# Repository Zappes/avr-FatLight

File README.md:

The FatLight
======================================

What Is this?
-------------
Short: It's a controller board for RGB LED strips that has a bluetooth and some GPIO pins.

Long: I recently ordered everything needed for the creation of PCBs, i.e. a UV exposure unit,
an etching apparatus, chemicals, boards, the works. As a first project, I wanted to do something
that I could use, that I understood from the electronics perspective and that could easily be
done on a one-sided PCB without solder mask. A controller for RGB strips seemed to be a good idea, so here we go. :)

**WARNING IF YOU WANT TO BUILD THIS**
Make sure that the pinout of your Bluetooth module matches the pinout on the board. I have three different HC-05 modules in my parts bin, and every type has a different pinout ... This sucks enormously, and if I didn't have those modules lying around, I'd use a pure HC-05 module instead of the breakouts i have now.

How can I control it?
---------------------
It's simple. Connect to the FatLight using a serial terminal over the Bluetooth connection, connection parameters are 9600 8N1, no handshake. The modules have their default pin set to 1234, so use that pin. After connecting, the following commands are supported:

| Command    | Parameter | Description                           |
|------------|-----------|---------------------------------------|
| status     |           | Prints the current settings.          |
| mode       | 0-2       | 0: direct color, 1: fade, 2: random   |
| on         |           | Switches the light on                 | 
| off        |           | Switches the light off                |
| step       | 00-FF     | Size of the fading steps when fading  |
| set        | color     | Sets the target color in mode 0 and 1 |
| delay      | 00-FF     | Greater delays make slower fades      |
| level      | 00-FF     | Brightness in mode 2; 0 is random     |
| store      | 00-05     | Store current settings in slot 0-5    |
| load       | 00-05     | Load settings from slot 0-5           |   
| bt_getname |           | Prints the name of the BT module      |
| bt_setname | string    | Sets the name of the BT module        |
| bt_getpass |           | Prints the current BT PIN             |
| bt_setpass | string    | Sets the BT PIN; best use 4 digits    |

Color parameters are given as 24 bit hex codes, i.e. 00FF00 for green. Other numeric parameters are also in hex notation. String parameters may never contain whitespace.

Where can I learn more?
-----------------------
[There's a playlist on Youtube.](https://www.youtube.com/playlist?list=PLFFlJlvZ--Pn7IzDO5DFNhvppb0ZImLEq) It's in German, I'm afraid.

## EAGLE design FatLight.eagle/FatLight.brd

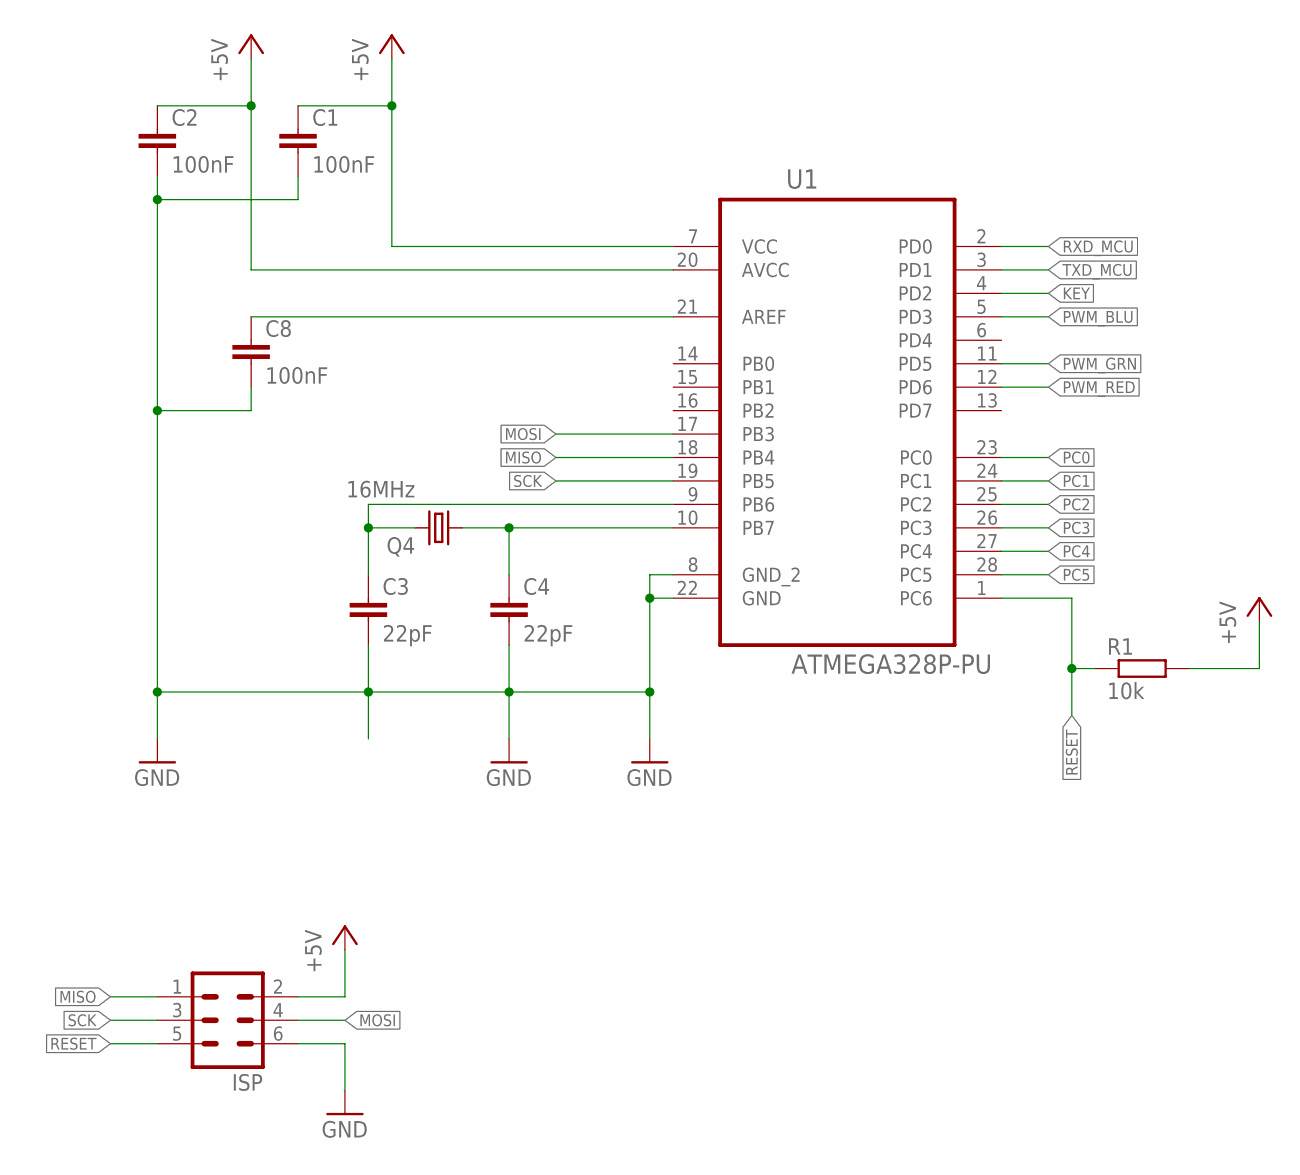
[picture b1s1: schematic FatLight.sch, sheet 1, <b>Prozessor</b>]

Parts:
C1, C2, C8: 100nF; C025-025X050
C3, C4: 22pF; C025-025X050
ISP: ML6
Q4: 16MHz; HC49/S
R1: 10k; 0207/7
U1: ATMEGA328P-PU; DIP254P762X457-28

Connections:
+5V: C1.1, C2.1, ISP.2, R1.2, U1.7 (VCC), U1.20 (AVCC); also elsewhere on the board
GND: C1.2, C2.2, C3.2, C4.2, C8.2, ISP.6, U1.8 (GND_2), U1.22 (GND); also elsewhere on the board
KEY: U1.4 (PD2); also elsewhere on the board
MISO: ISP.1, U1.18 (PB4)
MOSI: ISP.4, U1.17 (PB3)
unnamed: C4.1, Q4.1, U1.10 (PB7)
unnamed: C3.1, Q4.2, U1.9 (PB6)
unnamed: C8.1, U1.21 (AREF)
PC0: U1.23 (PC0); also elsewhere on the board
PC1: U1.24 (PC1); also elsewhere on the board
PC2: U1.25 (PC2); also elsewhere on the board
PC3: U1.26 (PC3); also elsewhere on the board
PC4: U1.27 (PC4); also elsewhere on the board
PC5: U1.28 (PC5); also elsewhere on the board
PWM_BLU: U1.5 (PD3); also elsewhere on the board
PWM_GRN: U1.11 (PD5); also elsewhere on the board
PWM_RED: U1.12 (PD6); also elsewhere on the board
RESET: ISP.5, R1.1, U1.1 (PC6)
RXD_MCU: U1.2 (PD0); also elsewhere on the board
SCK: ISP.3, U1.19 (PB5)
TXD_MCU: U1.3 (PD1); also elsewhere on the board

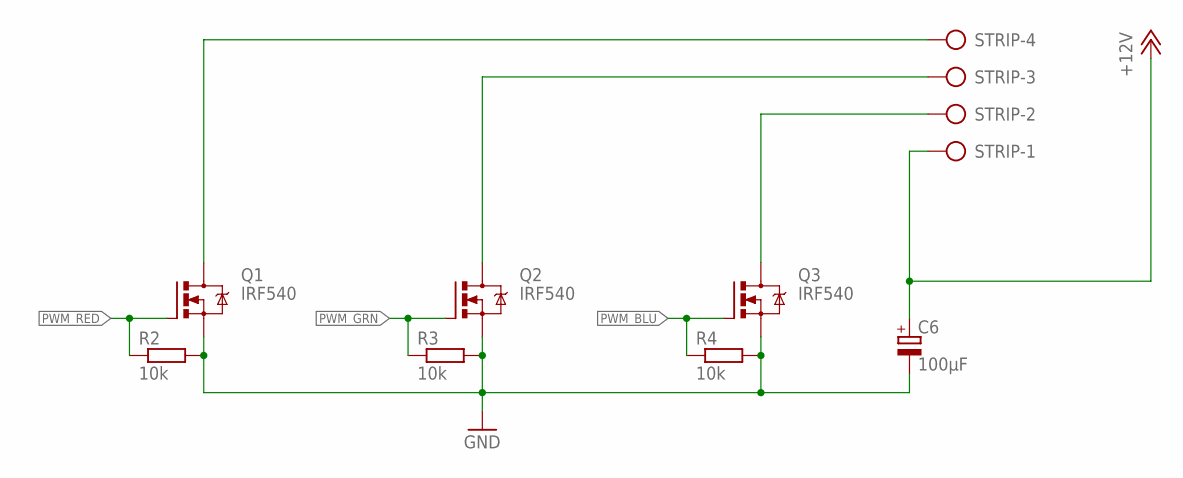
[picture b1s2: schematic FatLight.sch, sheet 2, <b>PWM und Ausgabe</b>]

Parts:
C6: 100µF; E2,5-5
Q1, Q2, Q3: IRF540; TO220BV
R2, R3, R4: 10k; 0207/7
STRIP: AK500/4

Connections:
+12V: C6.+, STRIP.1; also elsewhere on the board
GND: C6.-, Q1.S, Q2.S, Q3.S, R2.2, R3.2, R4.2; also elsewhere on the board
PWM_BLU: Q3.G, R4.1; also elsewhere on the board
PWM_GRN: Q2.G, R3.1; also elsewhere on the board
PWM_RED: Q1.G, R2.1; also elsewhere on the board
STRIP_BLU: Q3.D, STRIP.2
STRIP_GRN: Q2.D, STRIP.3
STRIP_RED: Q1.D, STRIP.4

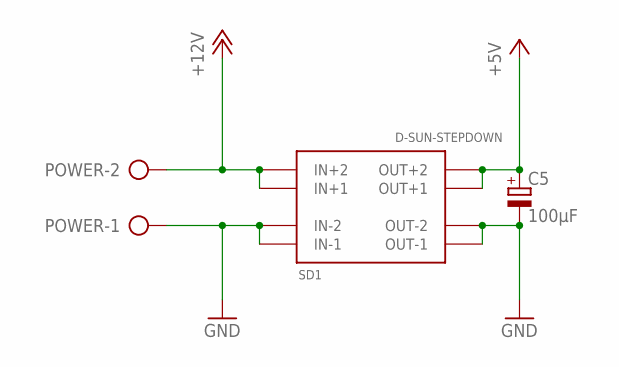
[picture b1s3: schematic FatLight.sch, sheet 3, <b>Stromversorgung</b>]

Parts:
C5: 100µF; E2,5-5
POWER: AK500/2
SD1: D-SUN-STEPDOWN; STEPDOWN-21X16

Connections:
+5V: C5.+, SD1.OUT+1, SD1.OUT+2; also elsewhere on the board
+12V: POWER.2, SD1.IN+1, SD1.IN+2; also elsewhere on the board
GND: C5.-, POWER.1, SD1.IN-1, SD1.IN-2, SD1.OUT-1, SD1.OUT-2; also elsewhere on the board

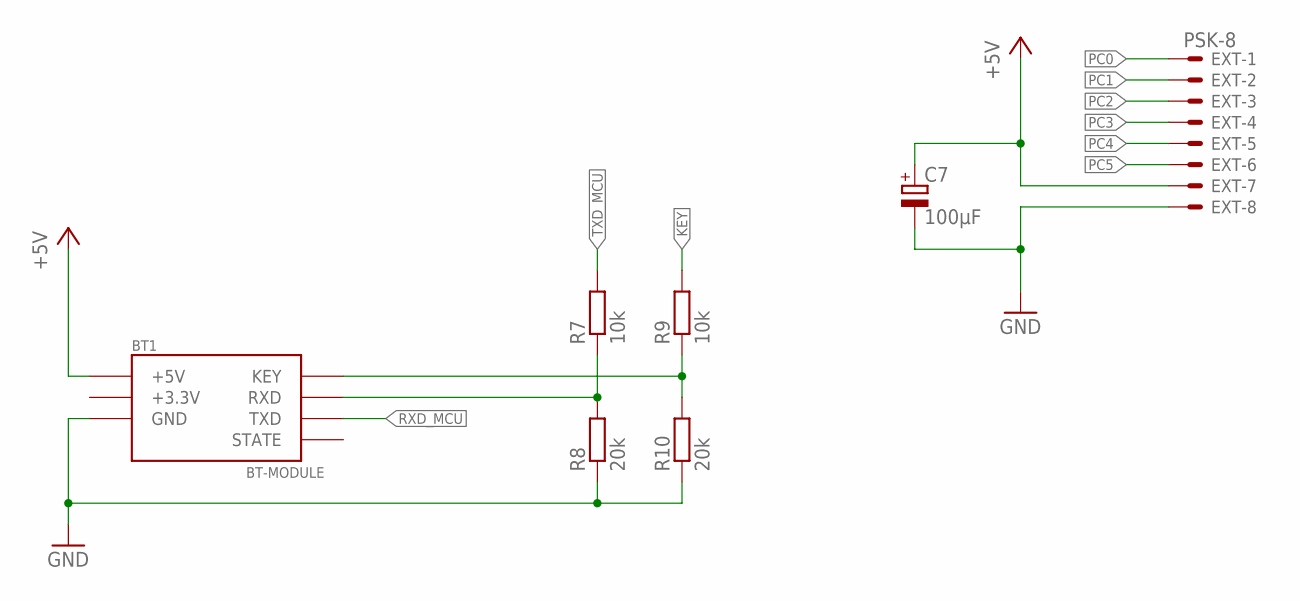
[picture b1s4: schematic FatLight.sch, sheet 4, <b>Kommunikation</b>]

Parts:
BT1: BT-MODULE; HC-05-6PIN
C7: 100µF; E2,5-5
EXT: PSK-8; 22-23-2081
R7, R9: 10k; 0207/7
R8, R10: 20k; 0207/7

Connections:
+3.3V: BT1.+3.3V
+5V: BT1.+5V, BT1.+5V1 (+5V), C7.+, EXT.7; also elsewhere on the board
GND: BT1.GND, BT1.GND1 (GND), C7.-, EXT.8, R8.1, R10.1; also elsewhere on the board
KEY: R9.2; also elsewhere on the board
unnamed: BT1.KEY, BT1.KEY1 (KEY), R9.1, R10.2
unnamed: BT1.RXD, BT1.RXD1 (RXD), R7.1, R8.2
PC0: EXT.1; also elsewhere on the board
PC1: EXT.2; also elsewhere on the board
PC2: EXT.3; also elsewhere on the board
PC3: EXT.4; also elsewhere on the board
PC4: EXT.5; also elsewhere on the board
PC5: EXT.6; also elsewhere on the board
RXD_MCU: BT1.TXD, BT1.TXD1 (TXD); also elsewhere on the board
TXD_MCU: R7.2; also elsewhere on the board

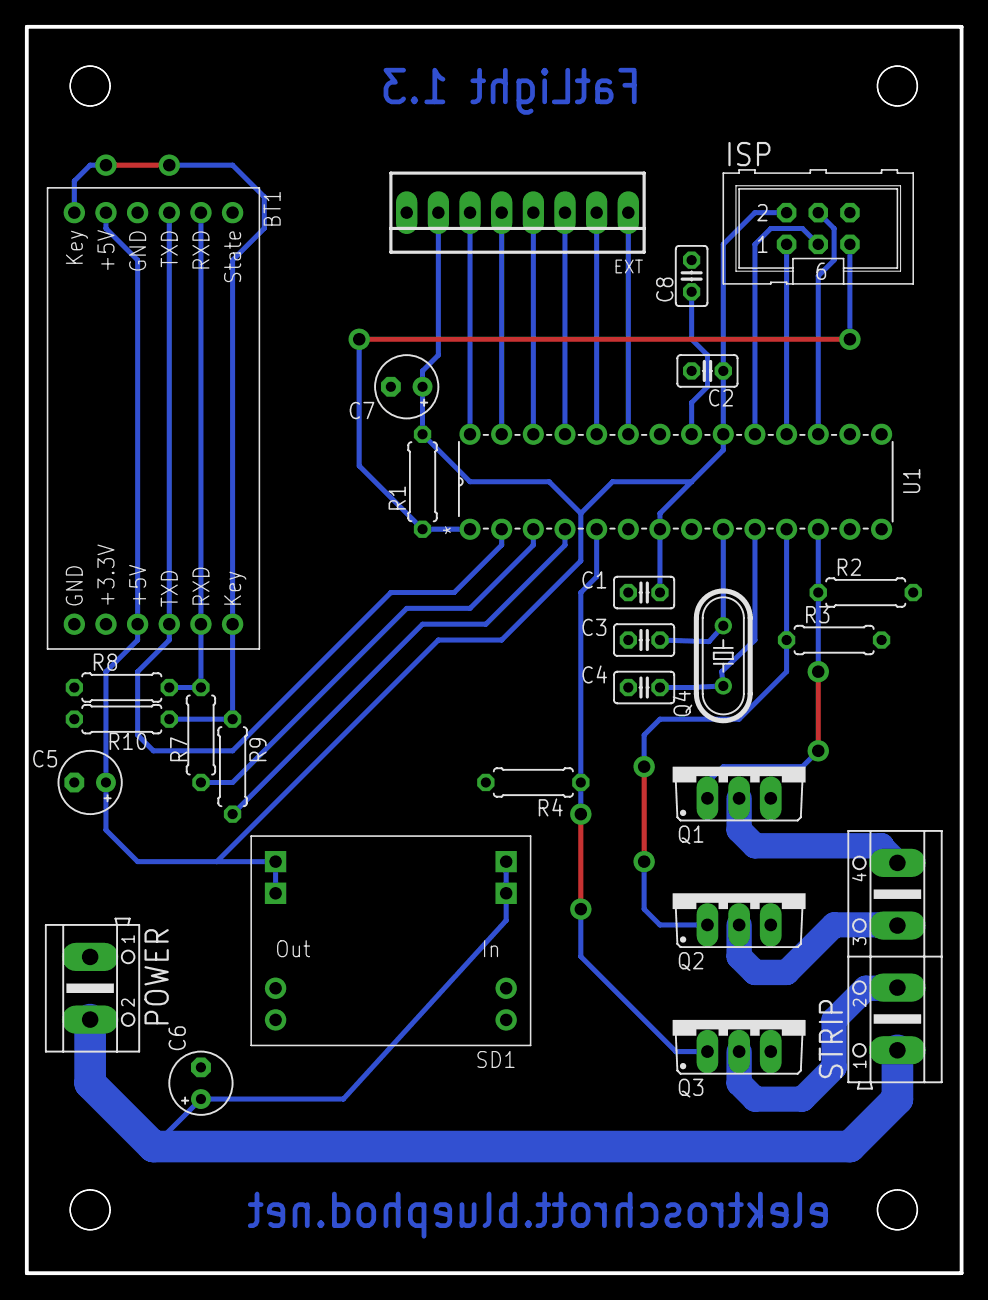
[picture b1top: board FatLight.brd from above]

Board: 2 copper layers, 75.0 x 100.0 mm, 27 parts (0 on the bottom side), 27 nets.

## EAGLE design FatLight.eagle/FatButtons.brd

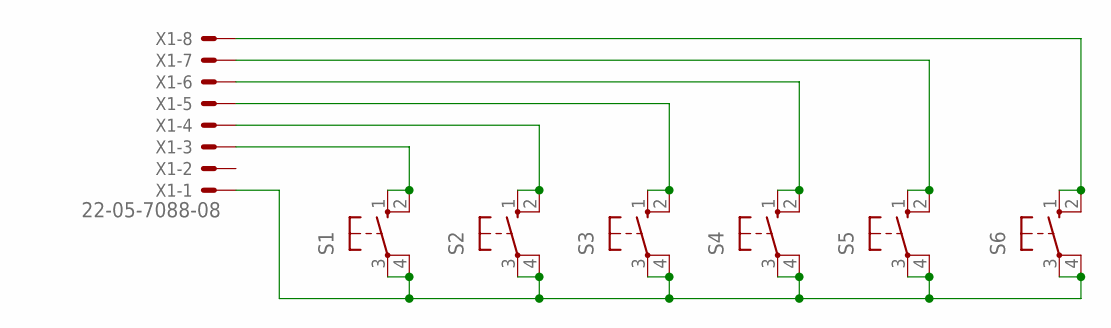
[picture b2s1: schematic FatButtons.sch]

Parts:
S1, S2, S3, S4, S5, S6: 10-XX; B3F-10XX
X1: 22-05-7088-08; 7395-08

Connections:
unnamed: S1.3, S1.4 (P1), S2.3, S2.4 (P1), S3.3, S3.4 (P1), S4.3, S4.4 (P1), S5.3, S5.4 (P1), S6.3, S6.4 (P1), X1.1
unnamed: S1.1 (S), S1.2 (S1), X1.3
unnamed: S2.1 (S), S2.2 (S1), X1.4
unnamed: S3.1 (S), S3.2 (S1), X1.5
unnamed: S4.1 (S), S4.2 (S1), X1.6
unnamed: S5.1 (S), S5.2 (S1), X1.7
unnamed: S6.1 (S), S6.2 (S1), X1.8

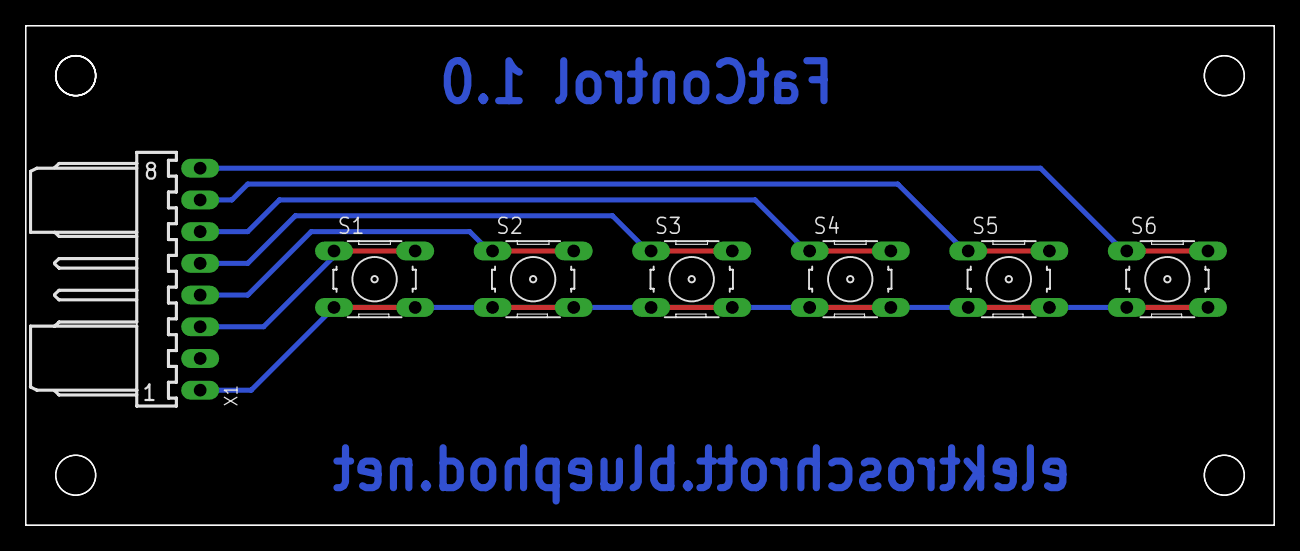
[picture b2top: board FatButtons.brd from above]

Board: 2 copper layers, 100.0 x 40.0 mm, 7 parts (0 on the bottom side), 7 nets.

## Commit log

2014-12-31 Bluetooth-Modul besser im Layout angeordnet.
2015-01-02 Vias und Restringe vergrößert, richtige Widerstandsgrößen verwendet, Platinengröße angepasst, Kondensator für Ext-Konnektor eingefügt.
2015-01-02 Optimierung des Boards
2015-01-04 Einfache Dummy-Firmware implementiert
2015-01-05 Implemented Bluetooth control
2015-01-05 Added animation code and support for renaming the BT device
2015-01-06 Cleaned up the command parser
2015-01-06 Added support for multiple stored profiles
2015-01-06 Added a pictire of the prototype
2015-01-07 Added support for Buttons on PC0-PC2 that can restore slots 0-2. (connect to GND)
2015-01-07 Optimized .gitignore so backups are ignored.
2015-01-07 Added disco mode for random color change
2015-01-07 Implemented support for custom animation step width
2015-01-08 Implemented proper communication with the bluetooth module
2015-01-08 Updated Board and Schmeatics so either of two different HC-05 module types can be fitted. Bugfixes.
2015-01-10 Implemented the on/off commands and remapped button 2 to power toggling instead of loading profile 2.
2015-01-10 Made sure that the corect color is used when re-enabling the strip after switching it off in disco mode.
2015-01-11 Changed the result format so every answer is exactly on eline, which is much easier to parse for clients.
2015-01-11 Lowered PWM frequency to 1kHz
2015-01-17 Cap setting for random values added, optimized board layout.
2015-01-18 Fixed the dimensions of the d-sun step-down module.
2015-01-25 Neue Revision des Boards, Firmware mit Farbeffekten
2015-01-28 Neue Board-Revision 1.3 mit stark optimiertem Layout und korrigiertem BT-Pinout
2015-01-28 Added a Youtube link
2015-01-28 Bestückungsdruck verbessert
2015-01-28 Postscript-Files für Masken aktualisiert
2015-02-05 FatButtons hinzugefügt, mehr Speicherlots freigegeben, Level 0 für Animationen mit zufälliger Helligkeit.
2015-02-16 Updated to revision 1.3
